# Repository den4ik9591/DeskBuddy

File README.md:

# DeskBuddy

A little desk robot with an animated screen face. It can turn, nod and tilt its head, blink, and change mood when you press the button on its base. It runs on a custom ESP32-S3 PCB I designed in KiCad, inside a 3D-printed case I designed in Fusion 360.

## How it works

- **Brain:** Waveshare ESP32-S3-Zero on a custom PCB, powered over USB-C.
- **Face:** 1.3" 240x240 ST7789 IPS screen over SPI. The firmware draws eyes and a mouth, with blinking and four moods (happy, sleepy, curious, surprised).
- **Movement:** three MG90S servos. Pan turns the neck, nod moves the head up and down, and tilt rolls the face sideways.
- **Power:** the servos run from a separate 5V supply through a screw terminal, with a 1000 µF capacitor to smooth out current spikes.
- **Button:** cycles through the moods.

| Part | GPIO |
|---|---|
| Servos: pan / nod / tilt | 4 / 5 / 6 |
| Button (to GND) | 7 |
| Screen: SCL / SDA / RES / DC / BLK | 12 / 11 / 9 / 10 / 8 |

## The case

The case has seven printed parts: base, lid, button plunger, neck, head pod, face shell and face back. I checked it in Fusion 360 with the real servo and screen models for collisions at pan ±80°, nod ±25° and tilt ±20°. It is toleranced for FDM printing, with servo pockets 0.5 mm wider than the servo, M2 pilot holes of 1.7 mm and 2 mm walls.

I first tried getting AI to make the case, but it was bad, so I redesigned it myself, which took ages.

## Files

- `Week4-DeskBuddy/Schematics/` KiCad schematic, PCB and STEP
- `Week4-DeskBuddy/Final files/` Fusion 360, STL and 3MF files, plus the Arduino code in `DeskBuddy/DeskBuddy.ino`
- `BOM.csv` bill of materials

## Build it

1. Order the PCB and the parts in `BOM.csv`, and print the case.
2. Solder everything onto the PCB.
3. In the Arduino IDE, install Adafruit GFX, Adafruit ST7735 and ST7789, and ESP32Servo.
4. Select "ESP32S3 Dev Module", turn on USB CDC On Boot, and upload the sketch.
5. Connect 5V to the screw terminal and assemble the case.

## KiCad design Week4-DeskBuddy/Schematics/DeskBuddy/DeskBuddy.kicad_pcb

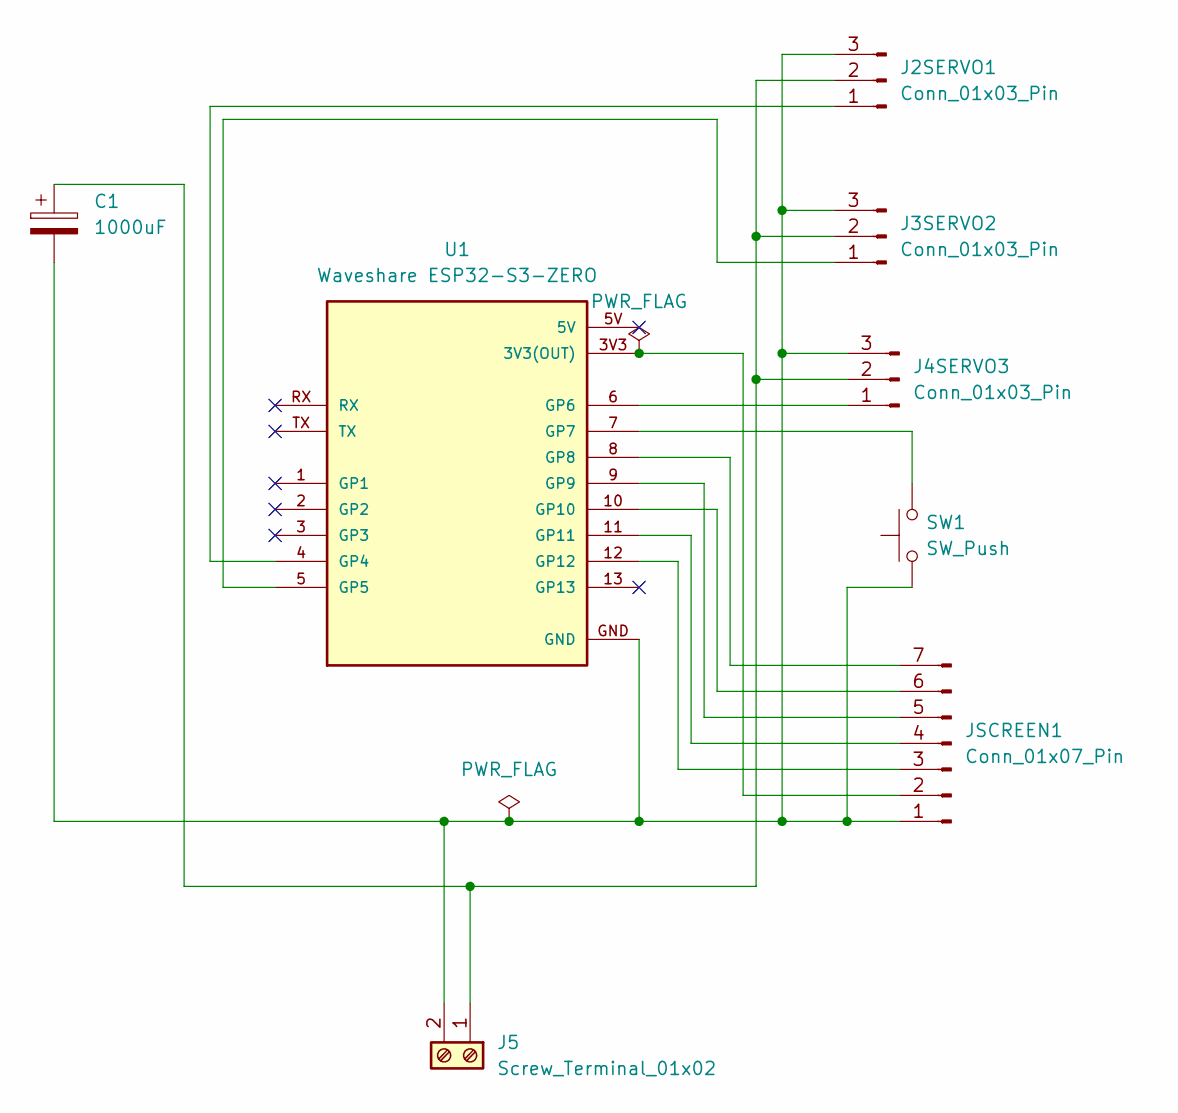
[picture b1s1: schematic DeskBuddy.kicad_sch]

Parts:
C1: 1000uF; CP_Radial_D8.0mm_P3.50mm
J2SERVO1, J3SERVO2, J4SERVO3: Conn_01x03_Pin; PinHeader_1x03_P2.54mm_Vertical
J5: Screw_Terminal_01x02; TerminalBlock_CUI_TB007-508-02_1x02_P5.08mm_Horizontal
JSCREEN1: Conn_01x07_Pin; PinHeader_1x07_P2.54mm_Vertical
SW1: SW_Push; SW_PUSH_6mm
U1: Waveshare ESP32-S3-ZERO; Waveshare ESP32-S3-Zero; PARTREV NA

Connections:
unnamed: J2SERVO1.1, U1.4 (GP4)
unnamed: C1.1, J2SERVO1.2, J3SERVO2.2, J4SERVO3.2, J5.1
unnamed: C1.2, J2SERVO1.3, J3SERVO2.3, J4SERVO3.3, J5.2, JSCREEN1.1, SW1.1, U1.GND
unnamed: J3SERVO2.1, U1.5 (GP5)
unnamed: J4SERVO3.1, U1.6 (GP6)
unnamed: JSCREEN1.2, U1.3V3 (3V3(OUT))
unnamed: JSCREEN1.3, U1.12 (GP12)
unnamed: JSCREEN1.4, U1.11 (GP11)
unnamed: JSCREEN1.5, U1.9 (GP9)
unnamed: JSCREEN1.6, U1.10 (GP10)
unnamed: JSCREEN1.7, U1.8 (GP8)
unnamed: SW1.2, U1.7 (GP7)

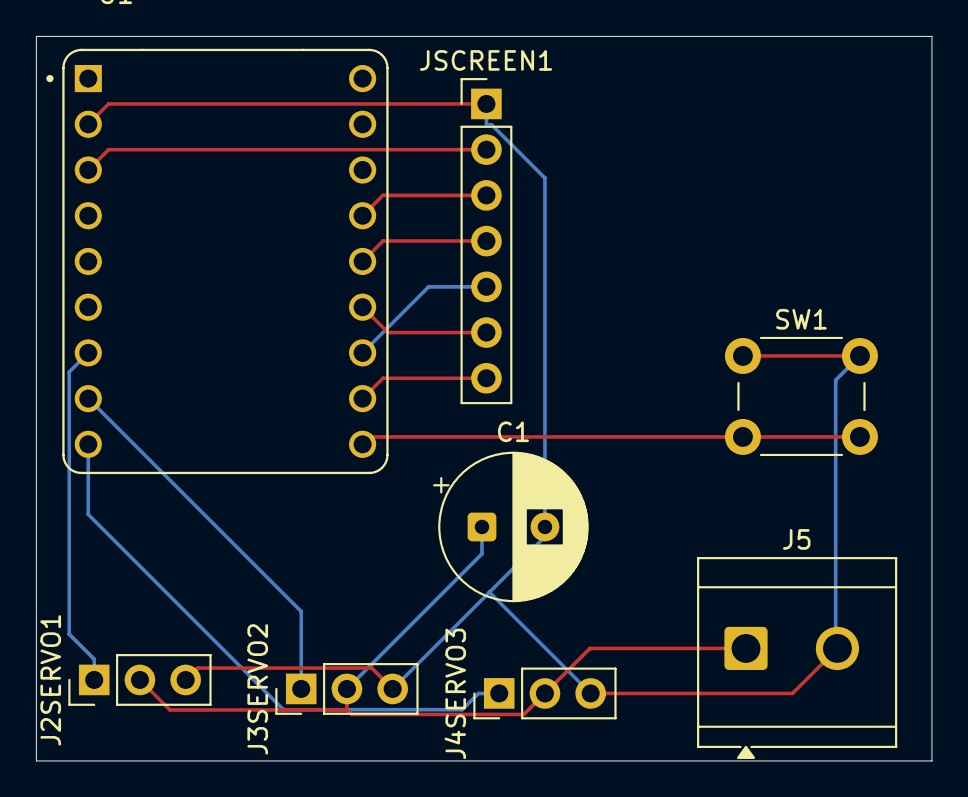
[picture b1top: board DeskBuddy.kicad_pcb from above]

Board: 2 copper layers, 49.8 x 40.2 mm, 8 parts (0 on the bottom side), 12 nets.
